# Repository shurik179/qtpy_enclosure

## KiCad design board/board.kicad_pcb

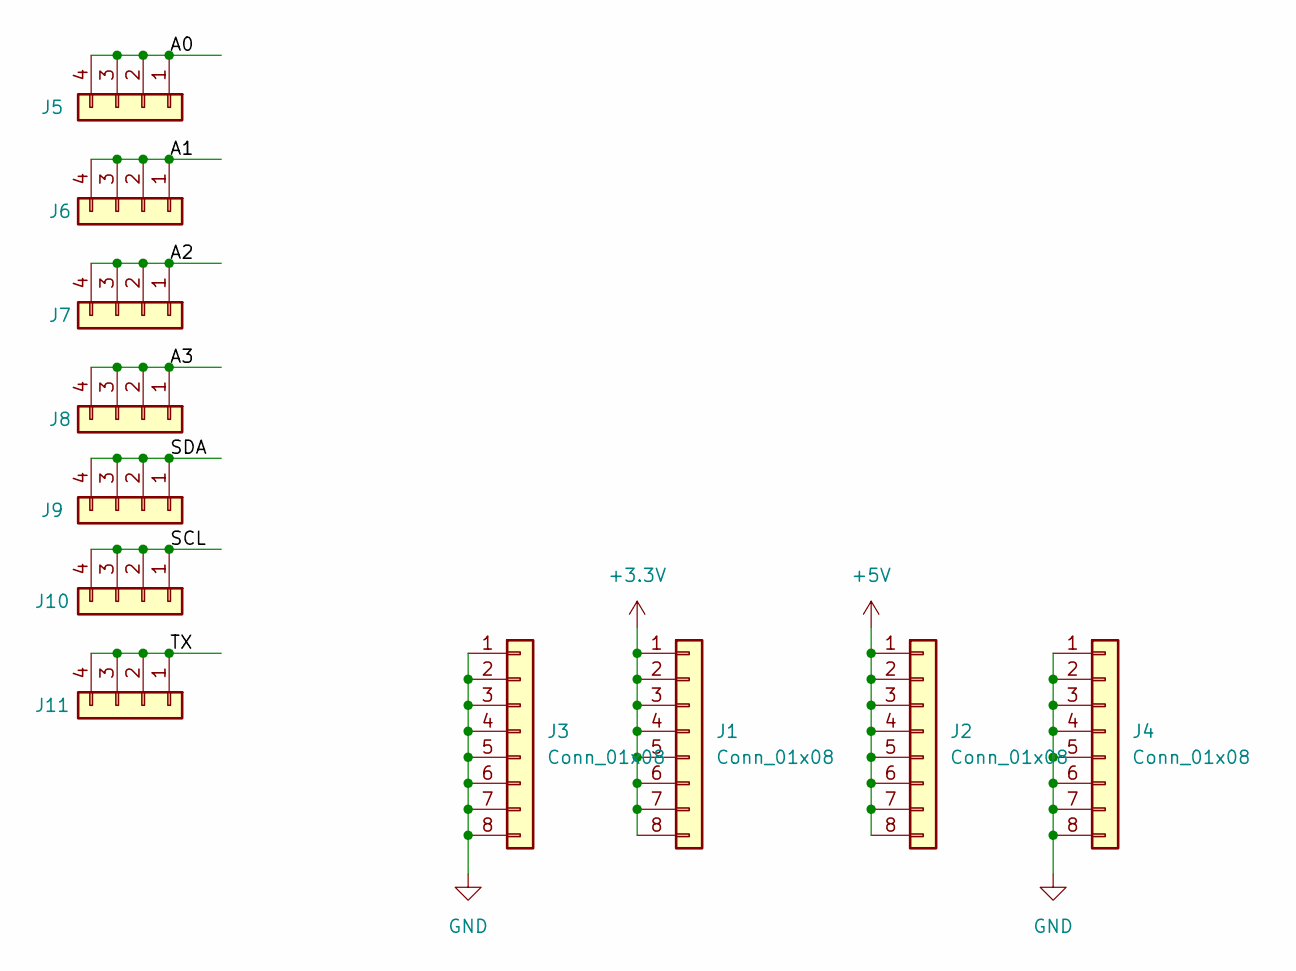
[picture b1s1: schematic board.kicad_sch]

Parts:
J1, J2, J3, J4: Conn_01x08; PinSocket_1x08_P2.54mm_Vertical
J5, J6, J7, J8, J9, J10, J11: Conn_01x04; PinHeader_1x04_P2.54mm_Vertical

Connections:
+3.3V: J1.1, J1.2, J1.3, J1.4, J1.5, J1.6, J1.7, J1.8
+5V: J2.1, J2.2, J2.3, J2.4, J2.5, J2.6, J2.7, J2.8
/A0: J5.1, J5.2, J5.3, J5.4
/A1: J6.1, J6.2, J6.3, J6.4
/A2: J7.1, J7.2, J7.3, J7.4
/A3: J8.1, J8.2, J8.3, J8.4
/SCL: J10.1, J10.2, J10.3, J10.4
/SDA: J9.1, J9.2, J9.3, J9.4
/TX: J11.1, J11.2, J11.3, J11.4
GND: J3.1, J3.2, J3.3, J3.4, J3.5, J3.6, J3.7, J3.8, J4.1, J4.2, J4.3, J4.4, J4.5, J4.6, J4.7, J4.8

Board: 2 copper layers, 11 parts (0 on the bottom side), 10 nets, no tracks yet.
